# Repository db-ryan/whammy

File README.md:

# Whammy-MIDI Interface

Takes a momantary footswitch up and down and turns it into
a MIDI signal for a Digitech Whammy.

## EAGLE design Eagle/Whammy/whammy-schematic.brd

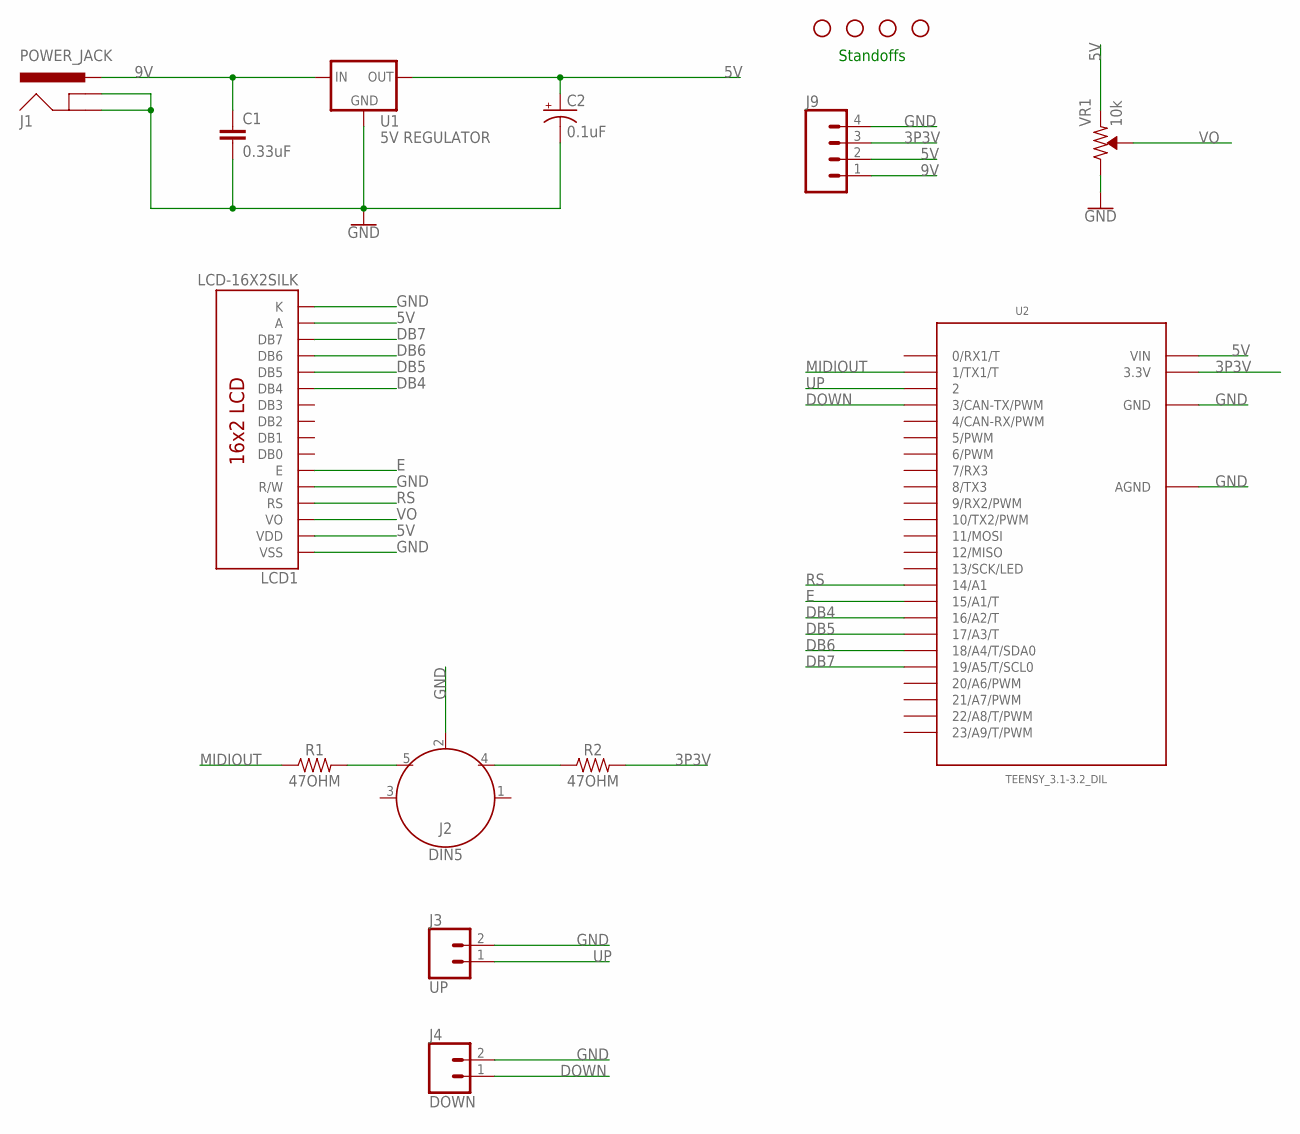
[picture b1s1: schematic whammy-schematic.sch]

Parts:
C1: 0.33uF; CAP-PTH-2.54
C2: 0.1uF; CPOL-RADIAL-2.5MM-5MM
H1, H2, H3, H4: STAND-OFF
J1: POWER_JACK; POWER_JACK_PTH
J2: DIN5; DIN5-RA-PTH
J3: UP; 1X02
J4: DOWN; 1X02
J9: CONN_04; 1X04
LCD1: LCD-16X2SILK; LCD-16X2
R1, R2: 47OHM; AXIAL-0.3-KIT
U1: 5V REGULATOR; TO-220-ALT
U2: TEENSY_3.1-3.2_DIL; TEENSY_3.0-3.2&LC_DIL
VR1: 10k; TRIMPOT-PTH-3386U

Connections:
3P3V: J9.3, R2.P$2 (2), U2.3.3V
5V: C2.1 (+), J9.2, LCD1.2 (VDD), LCD1.15 (A), U1.OUT, U2.VIN, VR1.1 (CCW)
9V: C1.1, J1.PWR, J9.1, U1.IN
DB4: LCD1.11 (DB4), U2.16/A2 (16/A2/T)
DB5: LCD1.12 (DB5), U2.17/A3 (17/A3/T)
DB6: LCD1.13 (DB6), U2.18/A4 (18/A4/T/SDA0)
DB7: LCD1.14 (DB7), U2.19/A5 (19/A5/T/SCL0)
DOWN: J4.1, U2.3 (3/CAN-TX/PWM)
E: LCD1.6 (E), U2.15/A1 (15/A1/T)
GND: C1.2, C2.2 (-), J1.GND, J1.GNDBREAK, J2.2, J3.2, J4.2, J9.4, LCD1.1 (VSS), LCD1.5 (R/W), LCD1.16 (K), U1.GND, U2.AGND, U2.GND, VR1.3 (CW)
MIDIOUT: R1.P$1 (1), U2.1 (1/TX1/T)
unnamed: J2.5, R1.P$2 (2)
unnamed: J2.4, R2.P$1 (1)
RS: LCD1.4 (RS), U2.14/A0 (14/A1)
UP: J3.1, U2.2
VO: LCD1.3 (VO), VR1.2 (WIPER)

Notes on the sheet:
Standoffs

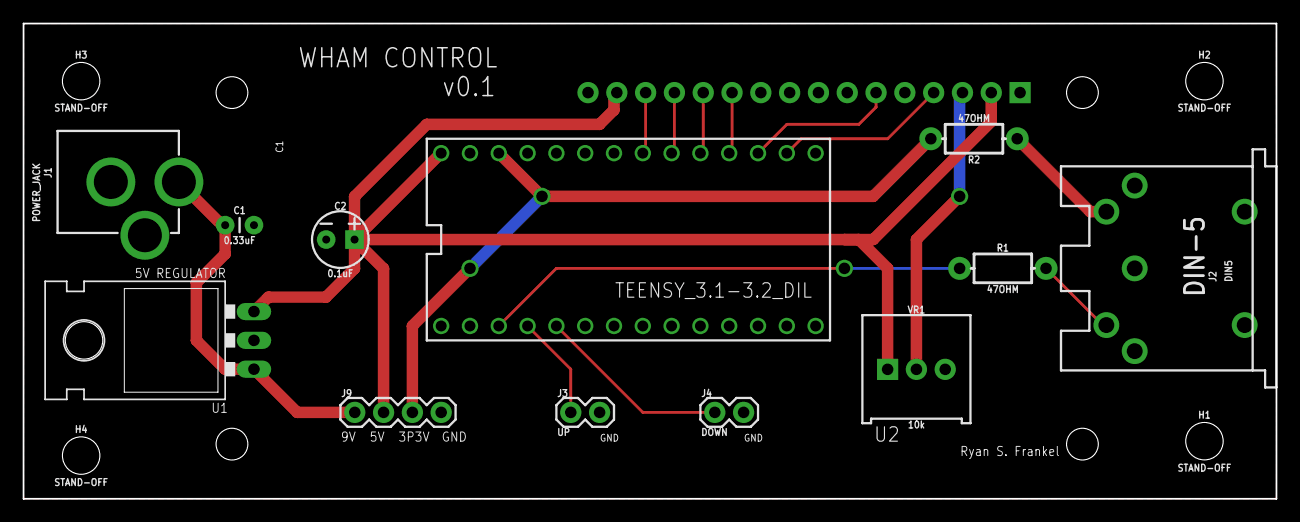
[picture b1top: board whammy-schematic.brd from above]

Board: 2 copper layers, 110.5 x 41.9 mm, 17 parts (1 on the bottom side), 16 nets.

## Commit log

2017-12-03 Initial commit.
2017-12-03 Fixed ++ and --.
2017-12-04 Added LCD.
2017-12-04 Rename for easy folder name.
2017-12-05 Adding LCD.
2017-12-06 Fixed comments. That's it. Sad commit.
2017-12-09 Minor.
2017-12-09 Fixed LCD to always write 16 characters.
2017-12-11 Updated to ignore revisions.
2017-12-11 Adding Eagle files.
2017-12-11 First version of schematic.
2017-12-11 Schematic and layout started.
2017-12-11 Initial layout commit. Nothing placed.
2017-12-12 Added initial layout. No ground fill yet.
2017-12-13 Finished board with planes. Including OSHPark design rules file.
2017-12-13 Adding images.

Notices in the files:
parts and their libraries:
SparkFun-Capacitors: Licensing: Creative Commons ShareAlike 4.0 International - https://creativecommons.org/licenses/by-sa/4.0
